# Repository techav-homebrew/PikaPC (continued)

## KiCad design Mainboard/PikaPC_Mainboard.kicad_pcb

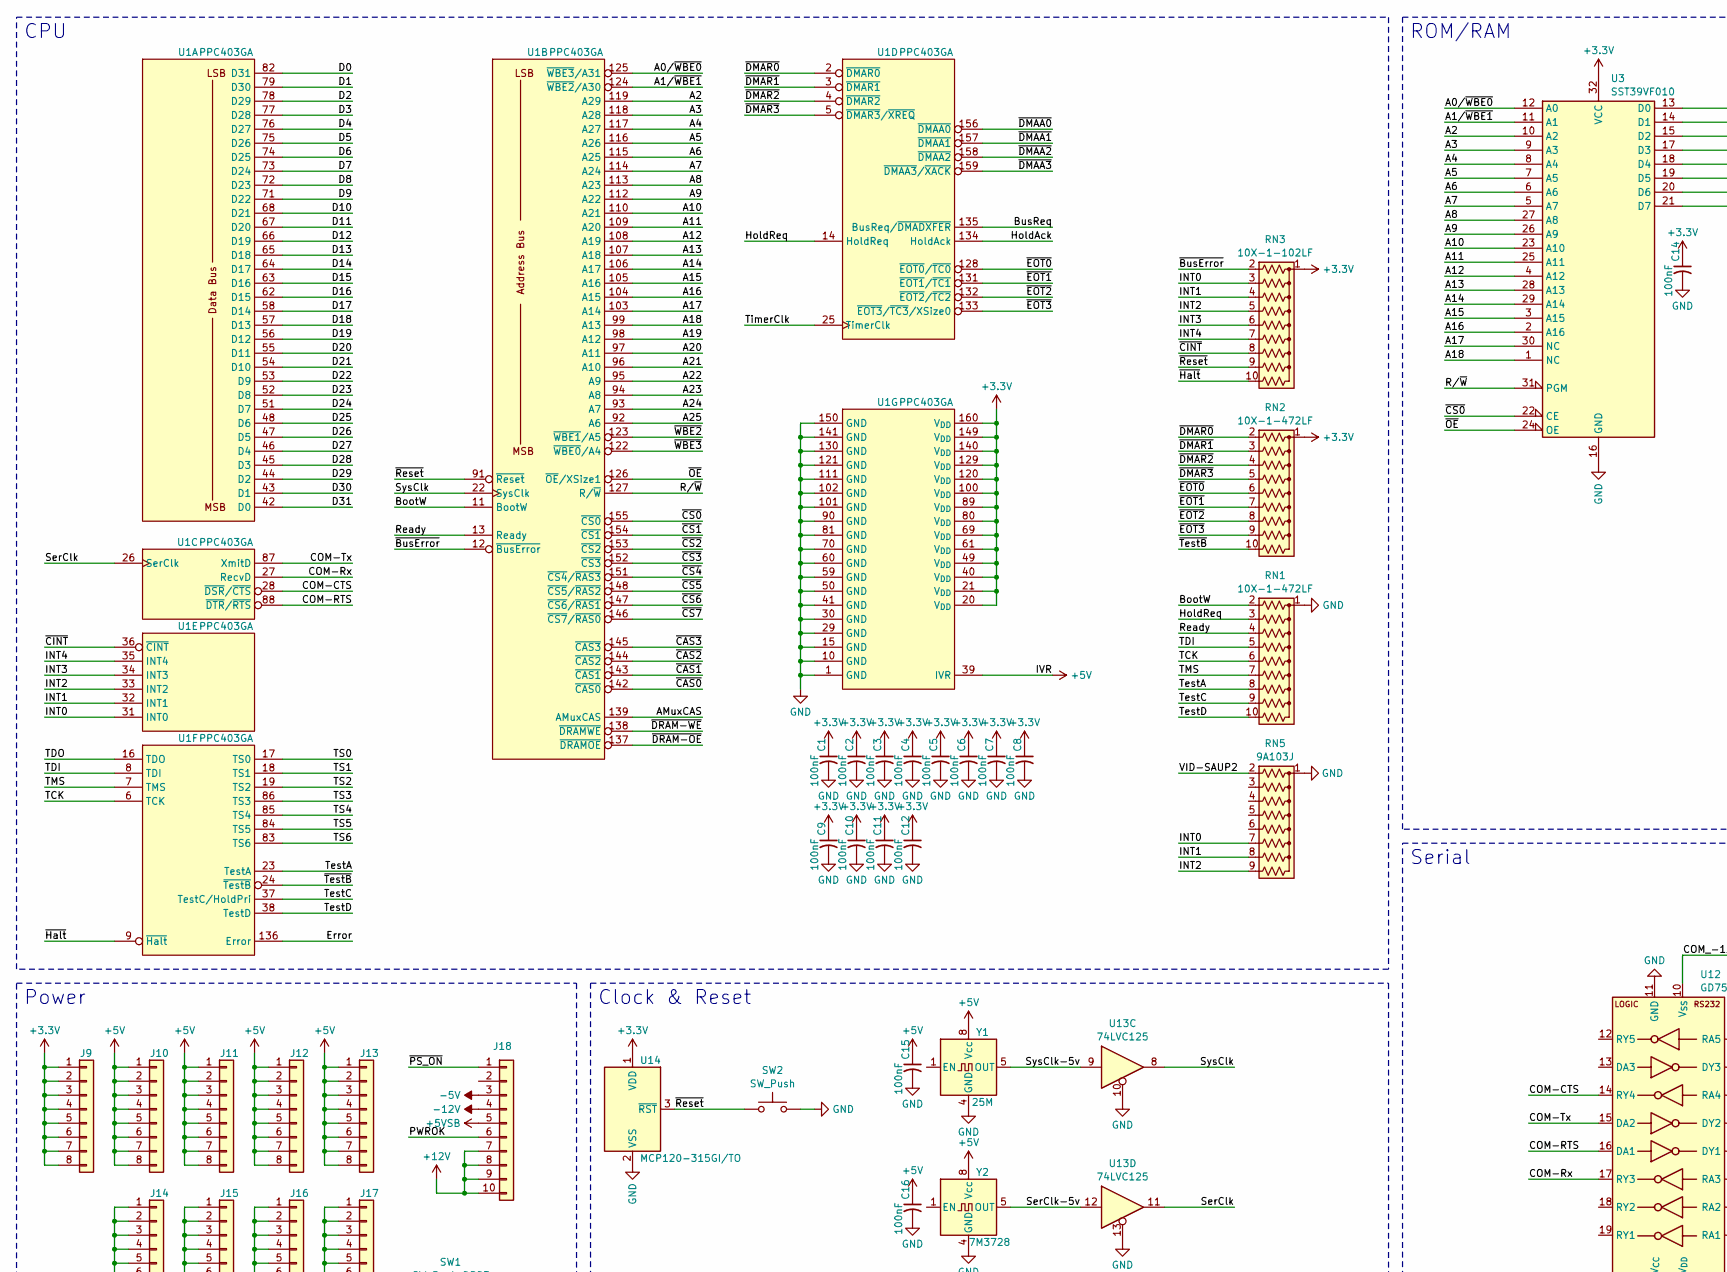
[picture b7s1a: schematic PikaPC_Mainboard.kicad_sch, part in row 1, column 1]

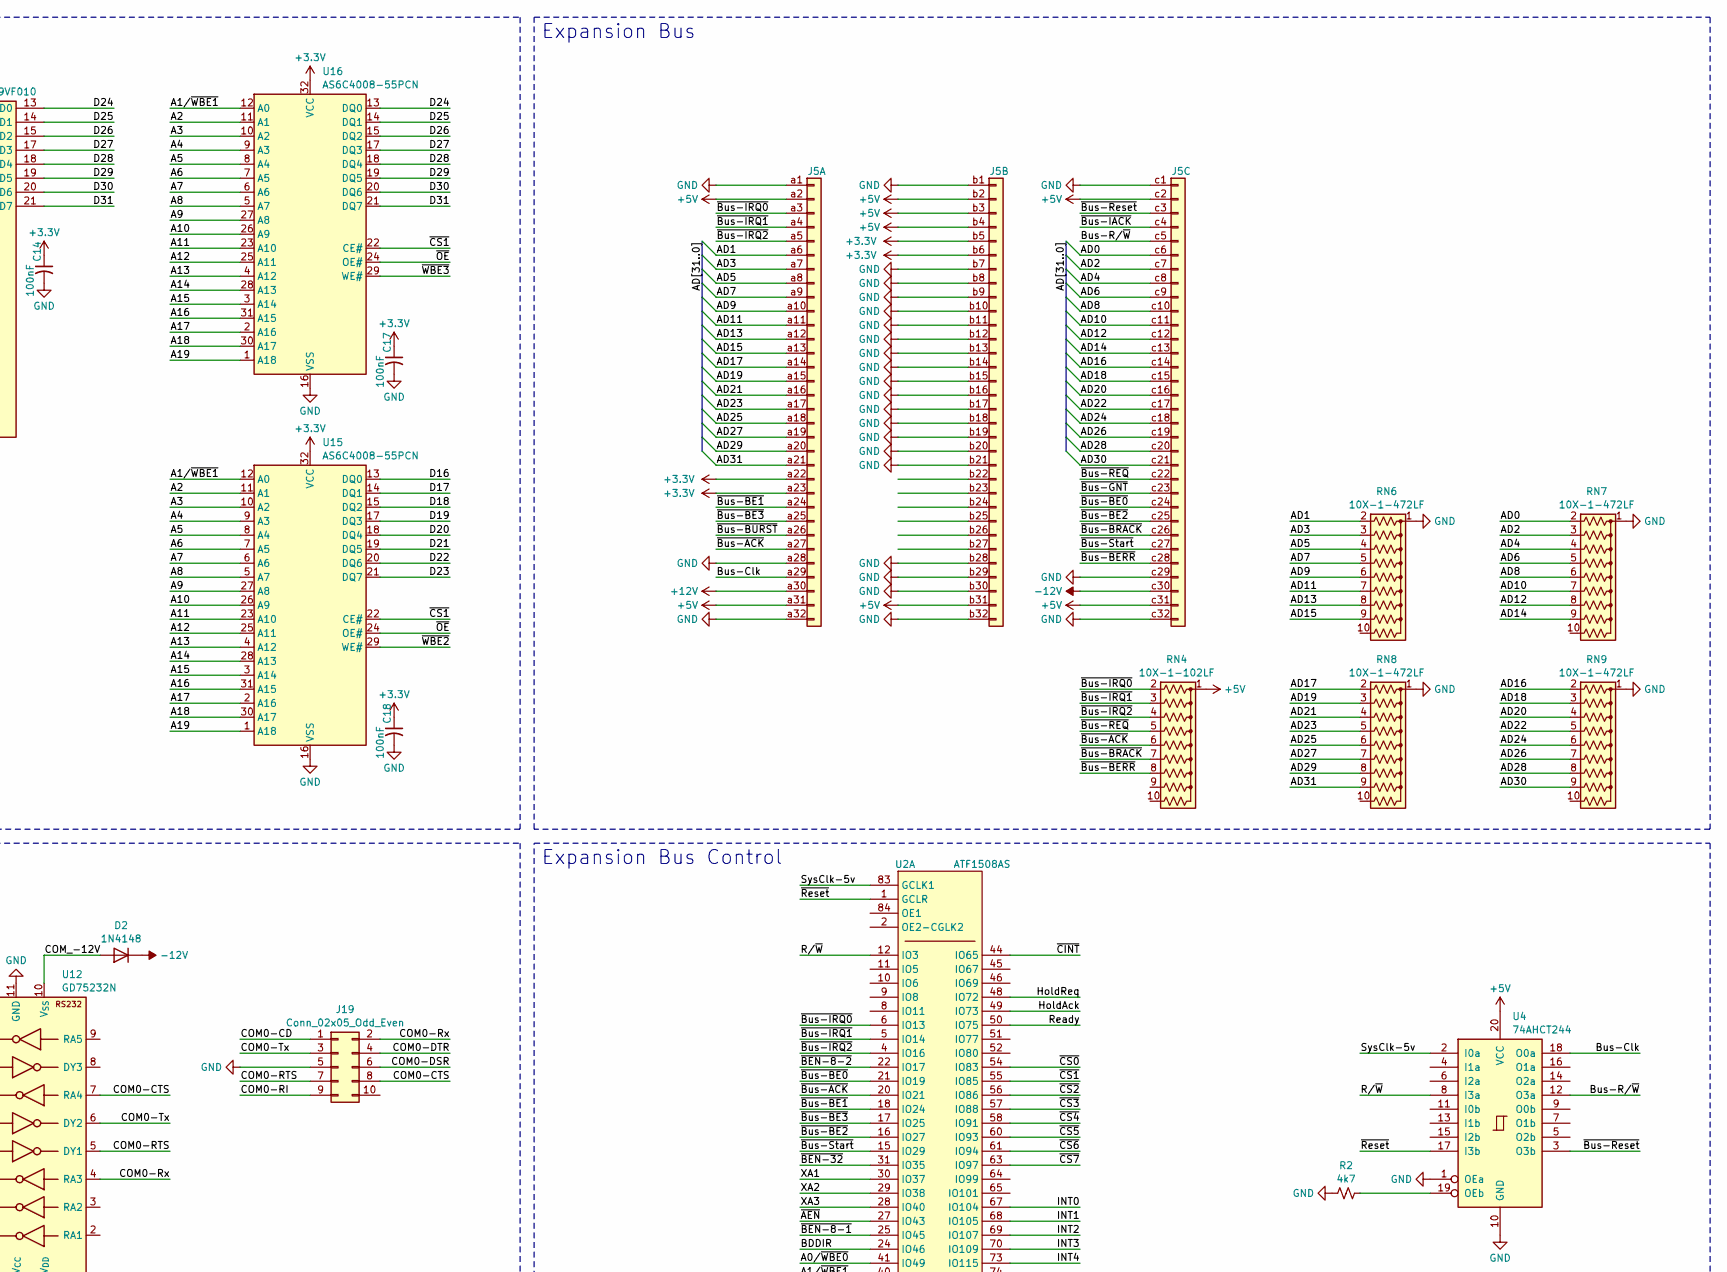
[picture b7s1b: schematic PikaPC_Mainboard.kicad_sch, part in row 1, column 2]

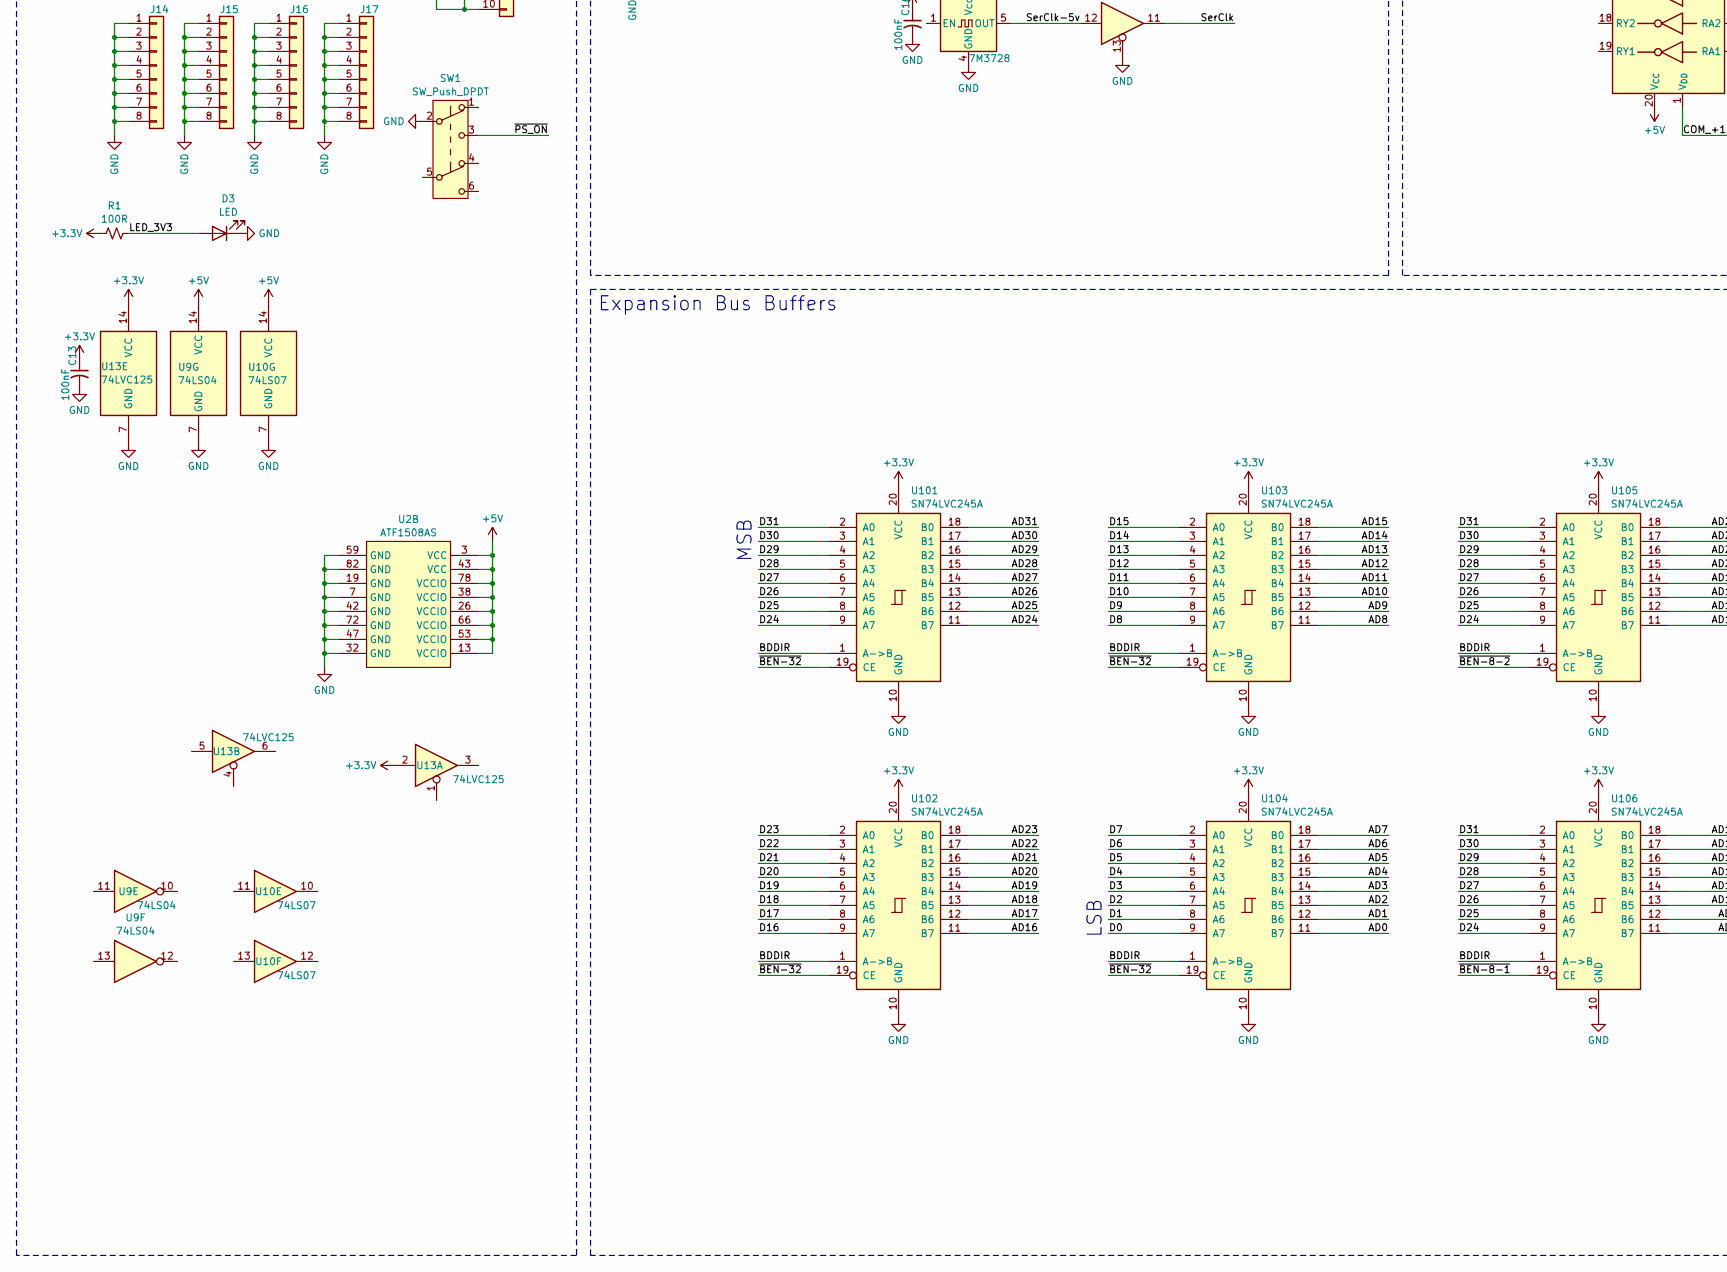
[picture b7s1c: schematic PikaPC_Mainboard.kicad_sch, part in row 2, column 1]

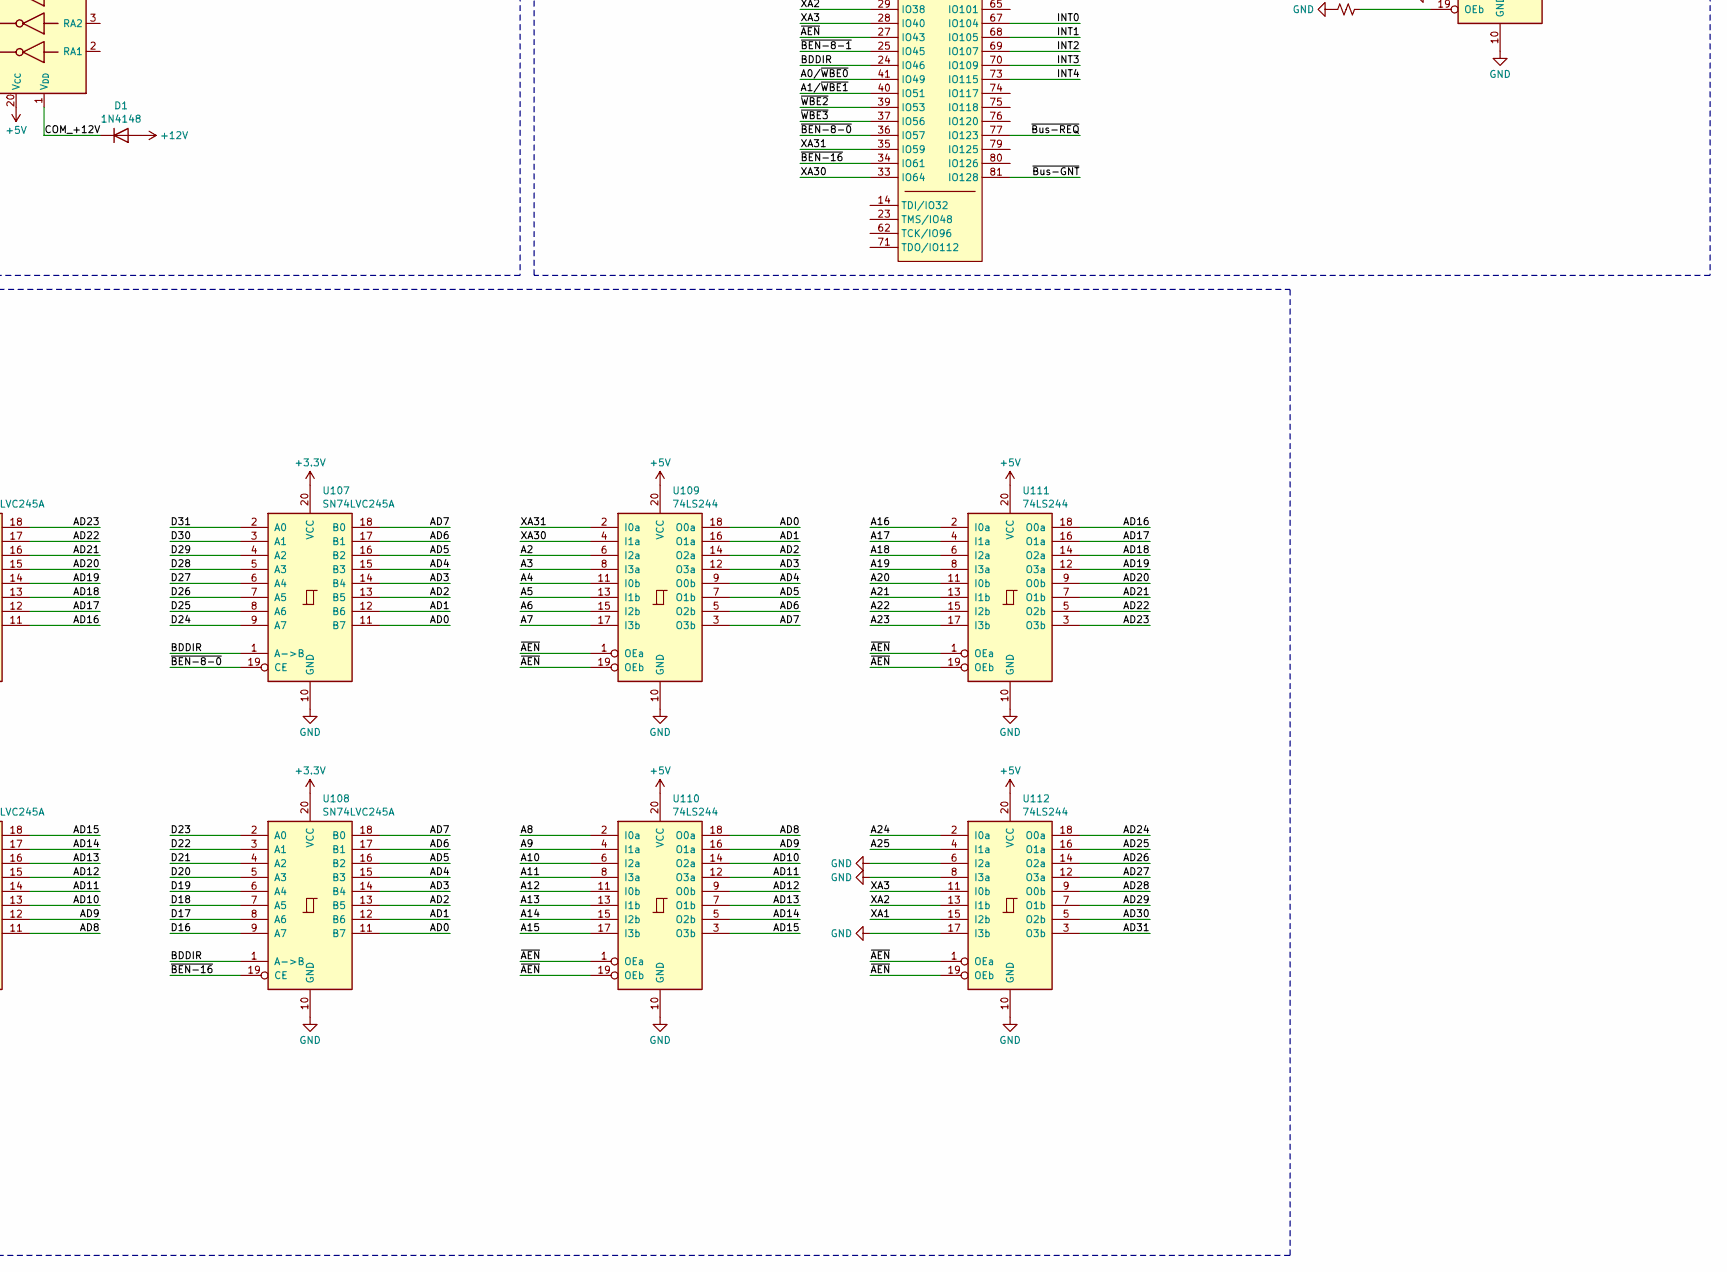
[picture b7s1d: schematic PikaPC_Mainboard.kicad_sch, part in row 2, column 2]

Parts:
C1, C2, C3, C4, C5, C6, C7, C8: 100nF; C_0805_2012Metric
C9, C10, C11, C12, C13: 100nF; C_Disc_D7.5mm_W5.0mm_P7.50mm
C14, C15, C16, C17, C18: 100nF; C_Disc_D3.0mm_W2.0mm_P2.50mm
D1, D2: 1N4148; D_DO-35_SOD27_P7.62mm_Horizontal
D3: LED; LED_D5.0mm
J5: DIN41612_03x32_C_Split; DIN41612_C_3x32_Female_Vertical_THT
J9, J10, J11, J12, J13, J14, J15, J16, J17: Conn_01x08; PinHeader_1x08_P2.54mm_Vertical
J18: Conn_01x10; PinHeader_1x10_P2.54mm_Vertical
J19: Conn_02x05_Odd_Even; PinHeader_2x05_P2.54mm_Vertical
R1: 100R; R_Axial_DIN0204_L3.6mm_D1.6mm_P2.54mm_Vertical
R2: 4k7; R_Axial_DIN0204_L3.6mm_D1.6mm_P7.62mm_Horizontal
RN1, RN2, RN6, RN7, RN8, RN9: 10X-1-472LF; R_Array_SIP10
RN3, RN4: 10X-1-102LF; R_Array_SIP10
RN5: 9A103J; R_Array_SIP9
SW1: SW_Push_DPDT; SW_CK_JS202011CQN_DPDT_Straight
SW2: SW_Push; SW_PUSH_6mm_H7.3mm
U1: PPC403GA; PQFP-160_28x28mm_P0.65mm
U2: ATF1508AS; PLCC-84_THT-Socket
U3: SST39VF010; PLCC-32_THT-Socket
U4: 74AHCT244; DIP-20_W7.62mm_Socket
U9: 74LS04; DIP-14_W7.62mm_Socket
U10: 74LS07; DIP-14_W7.62mm_Socket
U12: GD75232N; DIP-20_W7.62mm
U13: 74LVC125; DIP-14_W7.62mm_Socket
U14: MCP120-315GI/TO; TO-92_Inline_Wide
U15, U16: AS6C4008-55PCN; DIP-32_W15.24mm
U101, U102, U103, U104, U105, U106, U107, U108: SN74LVC245A; DIP-20_W7.62mm_Socket
U109, U110, U111, U112: 74LS244; DIP-20_W7.62mm_Socket
Y1: 25M; Oscillator_DIP-8
Y2: 7M3728; Oscillator_DIP-8

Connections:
+3.3V: C1.1, C2.1, C3.1, C4.1, C5.1, C6.1, C7.1, C8.1, C9.1, C10.1, C11.1, C12.1, C13.1, C14.1, C17.1, C18.1, J5.a22, J5.a23, J5.b5, J5.b6, J9.1, J9.2, J9.3, J9.4, J9.5, J9.6, J9.7, J9.8, R1.1, RN2.1 (common), RN3.1 (common), U1.20 (V_{DD}), U1.21 (V_{DD}), U1.40 (V_{DD}), U1.49 (V_{DD}), U1.61 (V_{DD}), U1.69 (V_{DD}), U1.80 (V_{DD}), U1.89 (V_{DD}), U1.100 (V_{DD}), U1.120 (V_{DD}), U1.129 (V_{DD}), U1.140 (V_{DD}), U1.149 (V_{DD}), U1.160 (V_{DD}), U3.32 (VCC), U13.2, U13.14 (VCC), U14.1 (VDD), U15.32 (VCC), U16.32 (VCC), U101.20 (VCC), U102.20 (VCC), U103.20 (VCC), U104.20 (VCC), U105.20 (VCC), U106.20 (VCC), U107.20 (VCC), U108.20 (VCC)
+5V: C15.1, C16.1, J5.a2, J5.a31, J5.b2, J5.b3, J5.b4, J5.b31, J5.c2, J5.c31, J10.1, J10.2, J10.3, J10.4, J10.5, J10.6, J10.7, J10.8, J11.1, J11.2, J11.3, J11.4, J11.5, J11.6, J11.7, J11.8, J12.1, J12.2, J12.3, J12.4, J12.5, J12.6, J12.7, J12.8, J13.1, J13.2, J13.3, J13.4, J13.5, J13.6, J13.7, J13.8, RN4.1 (common), U1.39 (IVR), U2.3 (VCC), U2.13 (VCCIO), U2.26 (VCCIO), U2.38 (VCCIO), U2.43 (VCC), U2.53 (VCCIO), U2.66 (VCCIO), U2.78 (VCCIO), U4.20 (VCC), U9.14 (VCC), U10.14 (VCC), U12.20 (V_{CC}), U109.20 (VCC), U110.20 (VCC), U111.20 (VCC), U112.20 (VCC), Y1.8 (Vcc), Y2.8 (Vcc)
+5VSB: J18.5
+12V: D1.2 (A), J5.a30, J18.7, J18.8, J18.9, J18.10
-5V: J18.3
-12V: D2.1 (K), J5.c30, J18.4
/A0/~WBE0: U1.125 (~WBE3/A31), U2.41 (IO49), U3.12 (A0)
/A1/~WBE1: U1.124 (~WBE2/A30), U2.40 (IO51), U3.11 (A1), U15.12 (A0), U16.12 (A0)
/A2: U1.119 (A29), U3.10 (A2), U15.11 (A1), U16.11 (A1), U109.6 (I2a)
/A3: U1.118 (A28), U3.9 (A3), U15.10 (A2), U16.10 (A2), U109.8 (I3a)
/A4: U1.117 (A27), U3.8 (A4), U15.9 (A3), U16.9 (A3), U109.11 (I0b)
/A5: U1.116 (A26), U3.7 (A5), U15.8 (A4), U16.8 (A4), U109.13 (I1b)
/A6: U1.115 (A25), U3.6 (A6), U15.7 (A5), U16.7 (A5), U109.15 (I2b)
/A7: U1.114 (A24), U3.5 (A7), U15.6 (A6), U16.6 (A6), U109.17 (I3b)
/A8: U1.113 (A23), U3.27 (A8), U15.5 (A7), U16.5 (A7), U110.2 (I0a)
/A9: U1.112 (A22), U3.26 (A9), U15.27 (A8), U16.27 (A8), U110.4 (I1a)
/A10: U1.110 (A21), U3.23 (A10), U15.26 (A9), U16.26 (A9), U110.6 (I2a)
/A11: U1.109 (A20), U3.25 (A11), U15.23 (A10), U16.23 (A10), U110.8 (I3a)
/A12: U1.108 (A19), U3.4 (A12), U15.25 (A11), U16.25 (A11), U110.11 (I0b)
/A13: U1.107 (A18), U3.28 (A13), U15.4 (A12), U16.4 (A12), U110.13 (I1b)
/A14: U1.106 (A17), U3.29 (A14), U15.28 (A13), U16.28 (A13), U110.15 (I2b)
/A15: U1.105 (A16), U3.3 (A15), U15.3 (A14), U16.3 (A14), U110.17 (I3b)
/A16: U1.104 (A15), U3.2 (A16), U15.31 (A15), U16.31 (A15), U111.2 (I0a)
/A17: U1.103 (A14), U3.30 (NC), U15.2 (A16), U16.2 (A16), U111.4 (I1a)
/A18: U1.99 (A13), U3.1 (NC), U15.30 (A17), U16.30 (A17), U111.6 (I2a)
/A19: U1.98 (A12), U15.1 (A18), U16.1 (A18), U111.8 (I3a)
/A20: U1.97 (A11), U111.11 (I0b)
/A21: U1.96 (A10), U111.13 (I1b)
/A22: U1.95 (A9), U111.15 (I2b)
/A23: U1.94 (A8), U111.17 (I3b)
/A24: U1.93 (A7), U112.2 (I0a)
/A25: U1.92 (A6), U112.4 (I1a)
/AD0: J5.c6, RN7.2 (R1), U104.11 (B7), U107.11 (B7), U108.11 (B7), U109.18 (O0a)
/AD1: J5.a6, RN6.2 (R1), U104.12 (B6), U107.12 (B6), U108.12 (B6), U109.16 (O1a)
/AD2: J5.c7, RN7.3 (R2), U104.13 (B5), U107.13 (B5), U108.13 (B5), U109.14 (O2a)
/AD3: J5.a7, RN6.3 (R2), U104.14 (B4), U107.14 (B4), U108.14 (B4), U109.12 (O3a)
/AD4: J5.c8, RN7.4 (R3), U104.15 (B3), U107.15 (B3), U108.15 (B3), U109.9 (O0b)
/AD5: J5.a8, RN6.4 (R3), U104.16 (B2), U107.16 (B2), U108.16 (B2), U109.7 (O1b)
/AD6: J5.c9, RN7.5 (R4), U104.17 (B1), U107.17 (B1), U108.17 (B1), U109.5 (O2b)
/AD7: J5.a9, RN6.5 (R4), U104.18 (B0), U107.18 (B0), U108.18 (B0), U109.3 (O3b)
/AD8: J5.c10, RN7.6 (R5), U103.11 (B7), U106.11 (B7), U110.18 (O0a)
/AD9: J5.a10, RN6.6 (R5), U103.12 (B6), U106.12 (B6), U110.16 (O1a)
/AD10: J5.c11, RN7.7 (R6), U103.13 (B5), U106.13 (B5), U110.14 (O2a)
/AD11: J5.a11, RN6.7 (R6), U103.14 (B4), U106.14 (B4), U110.12 (O3a)
/AD12: J5.c12, RN7.8 (R7), U103.15 (B3), U106.15 (B3), U110.9 (O0b)
/AD13: J5.a12, RN6.8 (R7), U103.16 (B2), U106.16 (B2), U110.7 (O1b)
/AD14: J5.c13, RN7.9 (R8), U103.17 (B1), U106.17 (B1), U110.5 (O2b)
/AD15: J5.a13, RN6.9 (R8), U103.18 (B0), U106.18 (B0), U110.3 (O3b)
/AD16: J5.c14, RN9.2 (R1), U102.11 (B7), U105.11 (B7), U111.18 (O0a)
/AD17: J5.a14, RN8.2 (R1), U102.12 (B6), U105.12 (B6), U111.16 (O1a)
/AD18: J5.c15, RN9.3 (R2), U102.13 (B5), U105.13 (B5), U111.14 (O2a)
/AD19: J5.a15, RN8.3 (R2), U102.14 (B4), U105.14 (B4), U111.12 (O3a)
/AD20: J5.c16, RN9.4 (R3), U102.15 (B3), U105.15 (B3), U111.9 (O0b)
/AD21: J5.a16, RN8.4 (R3), U102.16 (B2), U105.16 (B2), U111.7 (O1b)
/AD22: J5.c17, RN9.5 (R4), U102.17 (B1), U105.17 (B1), U111.5 (O2b)
/AD23: J5.a17, RN8.5 (R4), U102.18 (B0), U105.18 (B0), U111.3 (O3b)
/AD24: J5.c18, RN9.6 (R5), U101.11 (B7), U112.18 (O0a)
/AD25: J5.a18, RN8.6 (R5), U101.12 (B6), U112.16 (O1a)
/AD26: J5.c19, RN9.7 (R6), U101.13 (B5), U112.14 (O2a)
/AD27: J5.a19, RN8.7 (R6), U101.14 (B4), U112.12 (O3a)
/AD28: J5.c20, RN9.8 (R7), U101.15 (B3), U112.9 (O0b)
/AD29: J5.a20, RN8.8 (R7), U101.16 (B2), U112.7 (O1b)
/AD30: J5.c21, RN9.9 (R8), U101.17 (B1), U112.5 (O2b)
/AD31: J5.a21, RN8.9 (R8), U101.18 (B0), U112.3 (O3b)
/AMuxCAS: U1.139 (AMuxCAS)
/BDDIR: U2.24 (IO46), U101.1 (A->B), U102.1 (A->B), U103.1 (A->B), U104.1 (A->B), U105.1 (A->B), U106.1 (A->B), U107.1 (A->B), U108.1 (A->B)
/BootW: RN1.2 (R1), U1.11 (BootW)
/Bus-Clk: J5.a29, U4.18 (O0a)
/Bus-R/~W: J5.c5, U4.12 (O3a)
/BusReq: U1.135 (BusReq/~DMADXFER)
/COM0-CD: J19.1
/COM0-CTS: J19.8, U12.7 (RA4)
/COM0-DSR: J19.6
/COM0-DTR: J19.4
/COM0-RI: J19.9
/COM0-RTS: J19.7, U12.5 (DY1)
/COM0-Rx: J19.2, U12.4 (RA3)
/COM0-Tx: J19.3, U12.6 (DY2)
/COM-CTS: U1.28 (~DSR/~CTS), U12.14 (RY4)
/COM-RTS: U1.88 (~DTR/~RTS), U12.16 (DA1)
/COM-Rx: U1.27 (RecvD), U12.17 (RY3)
/COM-Tx: U1.87 (XmitD), U12.15 (DA2)
/COM_+12V: D1.1 (K), U12.1 (V_{DD})
/COM_-12V: D2.2 (A), U12.10 (V_{SS})
/D0: U1.82 (D31), U104.9 (A7)
/D1: U1.79 (D30), U104.8 (A6)
/D2: U1.78 (D29), U104.7 (A5)
/D3: U1.77 (D28), U104.6 (A4)
/D4: U1.76 (D27), U104.5 (A3)
/D5: U1.75 (D26), U104.4 (A2)
/D6: U1.74 (D25), U104.3 (A1)
/D7: U1.73 (D24), U104.2 (A0)
/D8: U1.72 (D23), U103.9 (A7)
/D9: U1.71 (D22), U103.8 (A6)
/D10: U1.68 (D21), U103.7 (A5)
/D11: U1.67 (D20), U103.6 (A4)
/D12: U1.66 (D19), U103.5 (A3)
/D13: U1.65 (D18), U103.4 (A2)
/D14: U1.64 (D17), U103.3 (A1)
/D15: U1.63 (D16), U103.2 (A0)
/D16: U1.62 (D15), U15.13 (DQ0), U102.9 (A7), U108.9 (A7)
/D17: U1.58 (D14), U15.14 (DQ1), U102.8 (A6), U108.8 (A6)
/D18: U1.57 (D13), U15.15 (DQ2), U102.7 (A5), U108.7 (A5)
/D19: U1.56 (D12), U15.17 (DQ3), U102.6 (A4), U108.6 (A4)
/D20: U1.55 (D11), U15.18 (DQ4), U102.5 (A3), U108.5 (A3)
/D21: U1.54 (D10), U15.19 (DQ5), U102.4 (A2), U108.4 (A2)
/D22: U1.53 (D9), U15.20 (DQ6), U102.3 (A1), U108.3 (A1)
/D23: U1.52 (D8), U15.21 (DQ7), U102.2 (A0), U108.2 (A0)
/D24: U1.51 (D7), U3.13 (D0), U16.13 (DQ0), U101.9 (A7), U105.9 (A7), U106.9 (A7), U107.9 (A7)
/D25: U1.48 (D6), U3.14 (D1), U16.14 (DQ1), U101.8 (A6), U105.8 (A6), U106.8 (A6), U107.8 (A6)
/D26: U1.47 (D5), U3.15 (D2), U16.15 (DQ2), U101.7 (A5), U105.7 (A5), U106.7 (A5), U107.7 (A5)
/D27: U1.46 (D4), U3.17 (D3), U16.17 (DQ3), U101.6 (A4), U105.6 (A4), U106.6 (A4), U107.6 (A4)
/D28: U1.45 (D3), U3.18 (D4), U16.18 (DQ4), U101.5 (A3), U105.5 (A3), U106.5 (A3), U107.5 (A3)
/D29: U1.44 (D2), U3.19 (D5), U16.19 (DQ5), U101.4 (A2), U105.4 (A2), U106.4 (A2), U107.4 (A2)
/D30: U1.43 (D1), U3.20 (D6), U16.20 (DQ6), U101.3 (A1), U105.3 (A1), U106.3 (A1), U107.3 (A1)
/D31: U1.42 (D0), U3.21 (D7), U16.21 (DQ7), U101.2 (A0), U105.2 (A0), U106.2 (A0), U107.2 (A0)
/Error: U1.136 (Error)
/HoldAck: U1.134 (HoldAck), U2.49 (IO73)
/HoldReq: RN1.3 (R2), U1.14 (HoldReq), U2.48 (IO72)
/INT0: RN3.3 (R2), RN5.7 (R6), U1.31 (INT0), U2.67 (IO104)
/INT1: RN3.4 (R3), RN5.8 (R7), U1.32 (INT1), U2.68 (IO105)
/INT2: RN3.5 (R4), RN5.9 (R8), U1.33 (INT2), U2.69 (IO107)
/INT3: RN3.6 (R5), U1.34 (INT3), U2.70 (IO109)
/INT4: RN3.7 (R6), U1.35 (INT4), U2.73 (IO115)
/LED_3V3: D3.2 (A), R1.2
/PWROK: J18.6
/Ready: RN1.4 (R3), U1.13 (Ready), U2.50 (IO75)
/R/~W: U1.127 (R/~W), U2.12 (IO3), U3.31 (PGM), U4.8 (I3a)
/SerClk: U1.26 (SerClk), U13.11
/SerClk-5v: U13.12, Y2.5 (OUT)
/SysClk: U1.22 (SysClk), U13.8
/SysClk-5v: U2.83 (GCLK1), U4.2 (I0a), U13.9, Y1.5 (OUT)
/TCK: RN1.6 (R5), U1.6 (TCK)
/TDI: RN1.5 (R4), U1.8 (TDI)
/TDO: U1.16 (TDO)
/TMS: RN1.7 (R6), U1.7 (TMS)
/TS0: U1.17 (TS0)
/TS1: U1.18 (TS1)
/TS2: U1.19 (TS2)
/TS3: U1.86 (TS3)
/TS4: U1.85 (TS4)
/TS5: U1.84 (TS5)
/TS6: U1.83 (TS6)
/TestA: RN1.8 (R7), U1.23 (TestA)
/TestC: RN1.9 (R8), U1.37 (TestC/HoldPri)
/TestD: RN1.10 (R9), U1.38 (TestD)
/TimerClk: U1.25 (TimerClk)
/VID-SAUP2: RN5.2 (R1)
/XA1: U2.30 (IO37), U112.15 (I2b)
/XA2: U2.29 (IO38), U112.13 (I1b)
/XA3: U2.28 (IO40), U112.11 (I0b)
/XA30: U2.33 (IO64), U109.4 (I1a)
/XA31: U2.35 (IO59), U109.2 (I0a)
/~AEN: U2.27 (IO43), U109.1 (OEa), U109.19 (OEb), U110.1 (OEa), U110.19 (OEb), U111.1 (OEa), U111.19 (OEb), U112.1 (OEa), U112.19 (OEb)
/~BEN-8-0: U2.36 (IO57), U107.19 (CE)
/~BEN-8-1: U2.25 (IO45), U106.19 (CE)
/~BEN-8-2: U2.22 (IO17), U105.19 (CE)
/~BEN-16: U2.34 (IO61), U108.19 (CE)
/~BEN-32: U2.31 (IO35), U101.19 (CE), U102.19 (CE), U103.19 (CE), U104.19 (CE)
/~Bus-ACK: J5.a27, RN4.6 (R5), U2.20 (IO21)
/~Bus-BE0: J5.c24, U2.21 (IO19)
/~Bus-BE1: J5.a24, U2.18 (IO24)
/~Bus-BE2: J5.c25, U2.16 (IO27)
/~Bus-BE3: J5.a25, U2.17 (IO25)
/~Bus-BERR: J5.c28, RN4.8 (R7)
/~Bus-BRACK: J5.c26, RN4.7 (R6)
/~Bus-BURST: J5.a26
/~Bus-GNT: J5.c23, U2.81 (IO128)
/~Bus-IACK: J5.c4
/~Bus-IRQ0: J5.a3, RN4.2 (R1), U2.6 (IO13)
/~Bus-IRQ1: J5.a4, RN4.3 (R2), U2.5 (IO14)
/~Bus-IRQ2: J5.a5, RN4.4 (R3), U2.4 (IO16)
/~Bus-REQ: J5.c22, RN4.5 (R4), U2.77 (IO123)
/~Bus-Reset: J5.c3, U4.3 (O3b)
/~Bus-Start: J5.c27, U2.15 (IO29)
/~BusError: RN3.2 (R1), U1.12 (~BusError)
/~CAS0: U1.142 (~CAS0)
/~CAS1: U1.143 (~CAS1)
/~CAS2: U1.144 (~CAS2)
/~CAS3: U1.145 (~CAS3)
/~CINT: RN3.8 (R7), U1.36 (~CINT), U2.44 (IO65)
/~CS0: U1.155 (~CS0), U2.54 (IO83), U3.22 (CE)
/~CS1: U1.154 (~CS1), U2.55 (IO85), U15.22 (CE#), U16.22 (CE#)
/~CS2: U1.153 (~CS2), U2.56 (IO86)
/~CS3: U1.152 (~CS3), U2.57 (IO88)
/~CS4: U1.151 (~CS4/~RAS3), U2.58 (IO91)
/~CS5: U1.148 (~CS5/~RAS2), U2.60 (IO93)
/~CS6: U1.147 (~CS6/~RAS1), U2.61 (IO94)
/~CS7: U1.146 (~CS7/~RAS0), U2.63 (IO97)
/~DMAA0: U1.156 (~DMAA0)
/~DMAA1: U1.157 (~DMAA1)
/~DMAA2: U1.158 (~DMAA2)
/~DMAA3: U1.159 (~DMAA3/~XACK)
/~DMAR0: RN2.2 (R1), U1.2 (~DMAR0)
/~DMAR1: RN2.3 (R2), U1.3 (~DMAR1)
/~DMAR2: RN2.4 (R3), U1.4 (~DMAR2)
/~DMAR3: RN2.5 (R4), U1.5 (~DMAR3/~XREQ)
/~DRAM-OE: U1.137 (~DRAMOE)
/~DRAM-WE: U1.138 (~DRAMWE)
/~EOT0: RN2.6 (R5), U1.128 (~EOT0/~TC0)
/~EOT1: RN2.7 (R6), U1.131 (~EOT1/~TC1)
/~EOT2: RN2.8 (R7), U1.132 (~EOT2/~TC2)
/~EOT3: RN2.9 (R8), U1.133 (~EOT3/~TC3/XSize0)
/~Halt: RN3.10 (R9), U1.9 (~Halt)
/~OE: U1.126 (~OE/XSize1), U3.24 (OE), U15.24 (OE#), U16.24 (OE#)
/~PS_ON: J18.1, SW1.3 (C)
/~Reset: RN3.9 (R8), SW2.2, U1.91 (~Reset), U2.1 (GCLR), U4.17 (I3b), U14.3 (~RST)
/~TestB: RN2.10 (R9), U1.24 (~TestB)
/~WBE2: U1.123 (~WBE1/A5), U2.39 (IO53), U15.29 (WE#)
/~WBE3: U1.122 (~WBE0/A4), U2.37 (IO56), U16.29 (WE#)
GND: C1.2, C2.2, C3.2, C4.2, C5.2, C6.2, C7.2, C8.2, C9.2, C10.2, C11.2, C12.2, C13.2, C14.2, C15.2, C16.2, C17.2, C18.2, D3.1 (K), J5.a1, J5.a28, J5.a32, J5.b1, J5.b7, J5.b8, J5.b9, J5.b10, J5.b11, J5.b12, J5.b13, J5.b14, J5.b15, J5.b16, J5.b17, J5.b18, J5.b19, J5.b20, J5.b21, J5.b28, J5.b29, J5.b30, J5.b32, J5.c1, J5.c29, J5.c32, J14.1, J14.2, J14.3, J14.4, J14.5, J14.6, J14.7, J14.8, J15.1, J15.2, J15.3, J15.4, J15.5, J15.6, J15.7, J15.8, J16.1, J16.2, J16.3, J16.4, J16.5, J16.6, J16.7, J16.8, J17.1, J17.2, J17.3, J17.4, J17.5, J17.6, J17.7, J17.8, J19.5, R2.1, RN1.1 (common), RN5.1 (common), RN6.1 (common), RN7.1 (common), RN8.1 (common), RN9.1 (common), SW1.2 (B), SW2.1, U1.1 (GND), U1.10 (GND), U1.15 (GND), U1.29 (GND), U1.30 (GND), U1.41 (GND), U1.50 (GND), U1.59 (GND), U1.60 (GND), U1.70 (GND), U1.81 (GND), U1.90 (GND), U1.101 (GND), U1.102 (GND), U1.111 (GND), U1.121 (GND), U1.130 (GND), U1.141 (GND), U1.150 (GND), U2.7 (GND), U2.19 (GND), U2.32 (GND), U2.42 (GND), U2.47 (GND), U2.59 (GND), U2.72 (GND), U2.82 (GND), U3.16 (GND), U4.1 (OEa), U4.10 (GND), U9.7 (GND), U10.7 (GND), U12.11 (GND), U13.7 (GND), U13.10, U13.13, U14.2 (VSS), U15.16 (VSS), U16.16 (VSS), U101.10 (GND), U102.10 (GND), U103.10 (GND), U104.10 (GND), U105.10 (GND), U106.10 (GND), U107.10 (GND), U108.10 (GND), U109.10 (GND), U110.10 (GND), U111.10 (GND), U112.6 (I2a), U112.8 (I3a), U112.10 (GND), U112.17 (I3b), Y1.4 (GND), Y2.4 (GND)
unnamed: R2.2, U4.19 (OEb)

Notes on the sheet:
Power
Expansion Bus Control
LSB
CPU
ROM/RAM
Serial
Expansion Bus
MSB
Clock & Reset
Expansion Bus Buffers

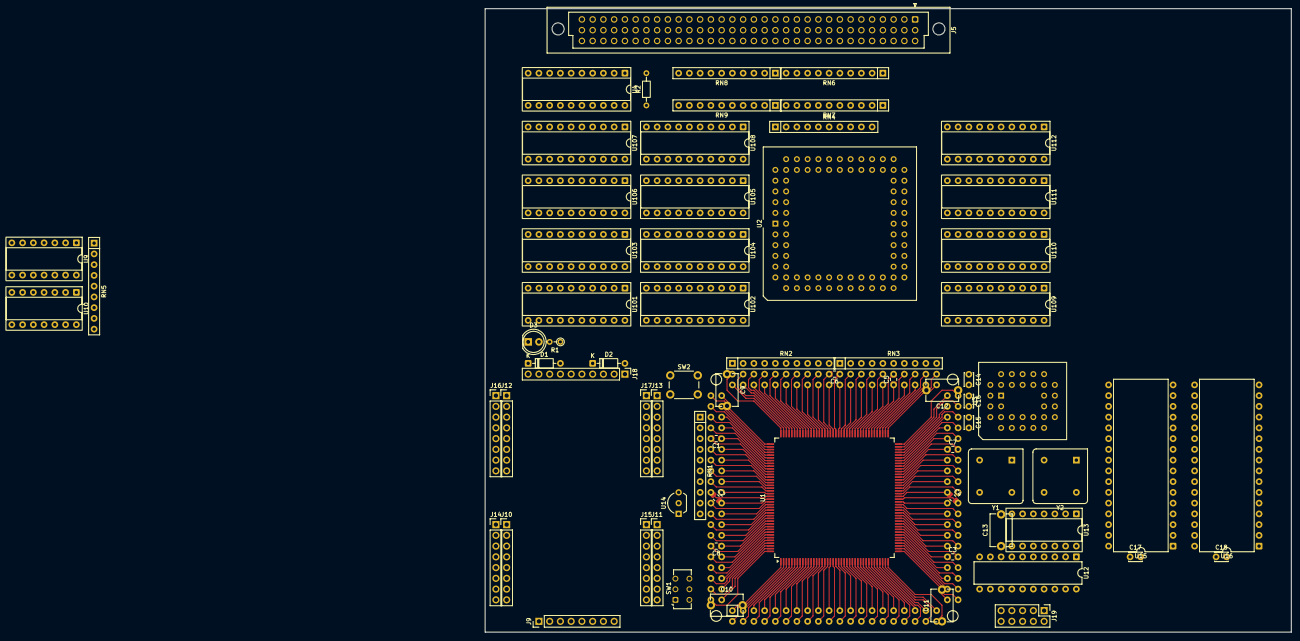
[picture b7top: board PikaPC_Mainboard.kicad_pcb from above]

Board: 2 copper layers, 190.5 x 147.3 mm, 71 parts (0 on the bottom side), 180 nets.

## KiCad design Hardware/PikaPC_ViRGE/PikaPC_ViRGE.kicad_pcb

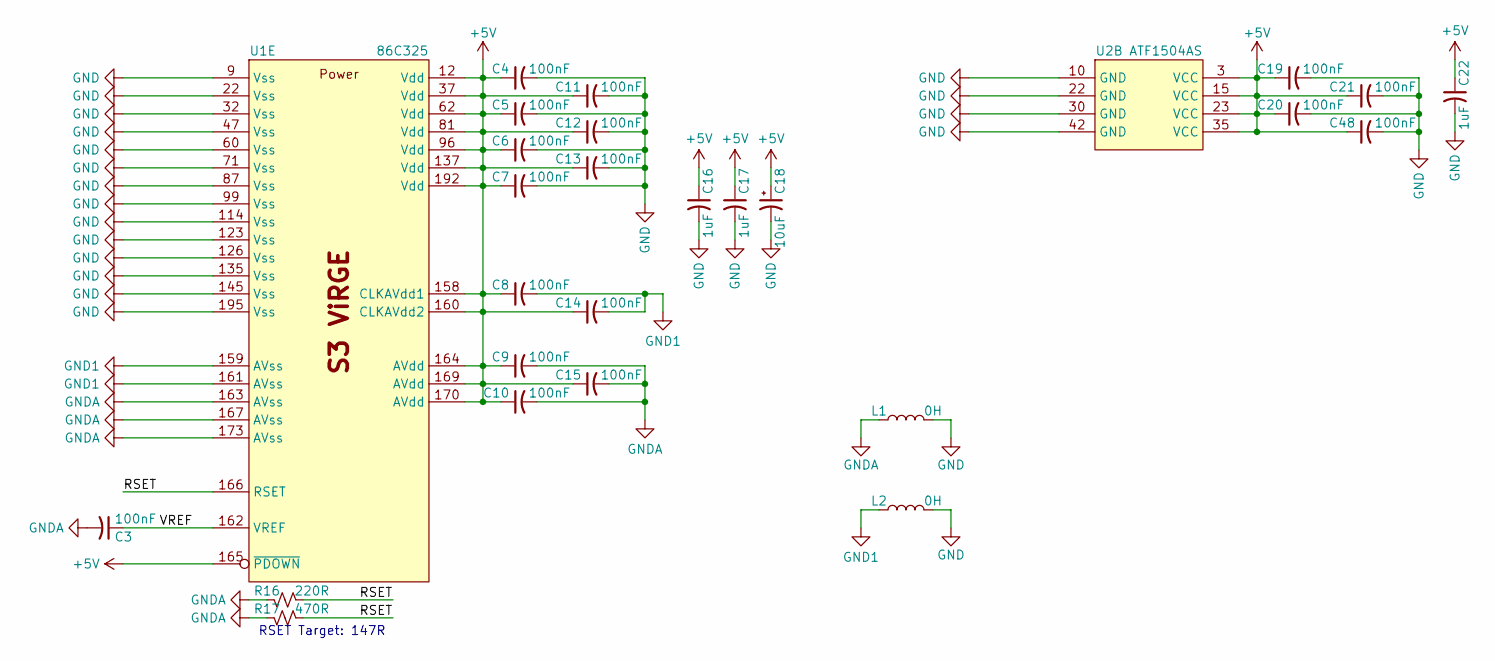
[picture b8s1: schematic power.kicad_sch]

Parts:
C3, C4, C5, C6, C7, C8, C9, C10, C11, C12, C13, C14, C15, C19, C20, C21, C48: 100nF; C_0805_2012Metric
C16, C17, C22: 1uF; C_0805_2012Metric
C18: 10uF; CP_Elec_4x5.7; Mouser 80-EDK106M016A9BAA
L1, L2: 0H; L_1210_3225Metric
R16: 220R; R_Axial_DIN0204_L3.6mm_D1.6mm_P2.54mm_Vertical
R17: 470R; R_Axial_DIN0204_L3.6mm_D1.6mm_P2.54mm_Vertical
U1: 86C325; PQFP-208_28x28mm_P0.5mm
U2: ATF1504AS; PLCC-44_THT-Socket

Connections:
+5V: C4.1, C5.1, C6.1, C7.1, C8.1, C9.1, C10.1, C11.1, C12.1, C13.1, C14.1, C15.1, C16.1, C17.1, C18.1, C19.1, C20.1, C21.1, C22.1, C48.1, U1.12 (Vdd), U1.37 (Vdd), U1.62 (Vdd), U1.81 (Vdd), U1.96 (Vdd), U1.137 (Vdd), U1.158 (CLKAVdd1), U1.160 (CLKAVdd2), U1.164 (AVdd), U1.165 (~PDOWN), U1.169 (AVdd), U1.170 (AVdd), U1.192 (Vdd), U2.3 (VCC), U2.15 (VCC), U2.23 (VCC), U2.35 (VCC); also elsewhere on the board
/Power/RSET: R16.1, R17.1, U1.166 (RSET); also elsewhere on the board
/Power/VREF: C3.1, U1.162 (VREF)
GND: C4.2, C5.2, C6.2, C7.2, C11.2, C12.2, C13.2, C16.2, C17.2, C18.2, C19.2, C20.2, C21.2, C22.2, C48.2, L1.2, L2.2, U1.9 (Vss), U1.22 (Vss), U1.32 (Vss), U1.47 (Vss), U1.60 (Vss), U1.71 (Vss), U1.87 (Vss), U1.99 (Vss), U1.114 (Vss), U1.123 (Vss), U1.126 (Vss), U1.135 (Vss), U1.145 (Vss), U1.195 (Vss), U2.10 (GND), U2.22 (GND), U2.30 (GND), U2.42 (GND); also elsewhere on the board
GND1: C8.2, C14.2, L2.1, U1.159 (AVss), U1.161 (AVss); also elsewhere on the board
GNDA: C3.2, C9.2, C10.2, C15.2, L1.1, R16.2, R17.2, U1.163 (AVss), U1.167 (AVss), U1.173 (AVss); also elsewhere on the board

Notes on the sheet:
RSET Target: 147R

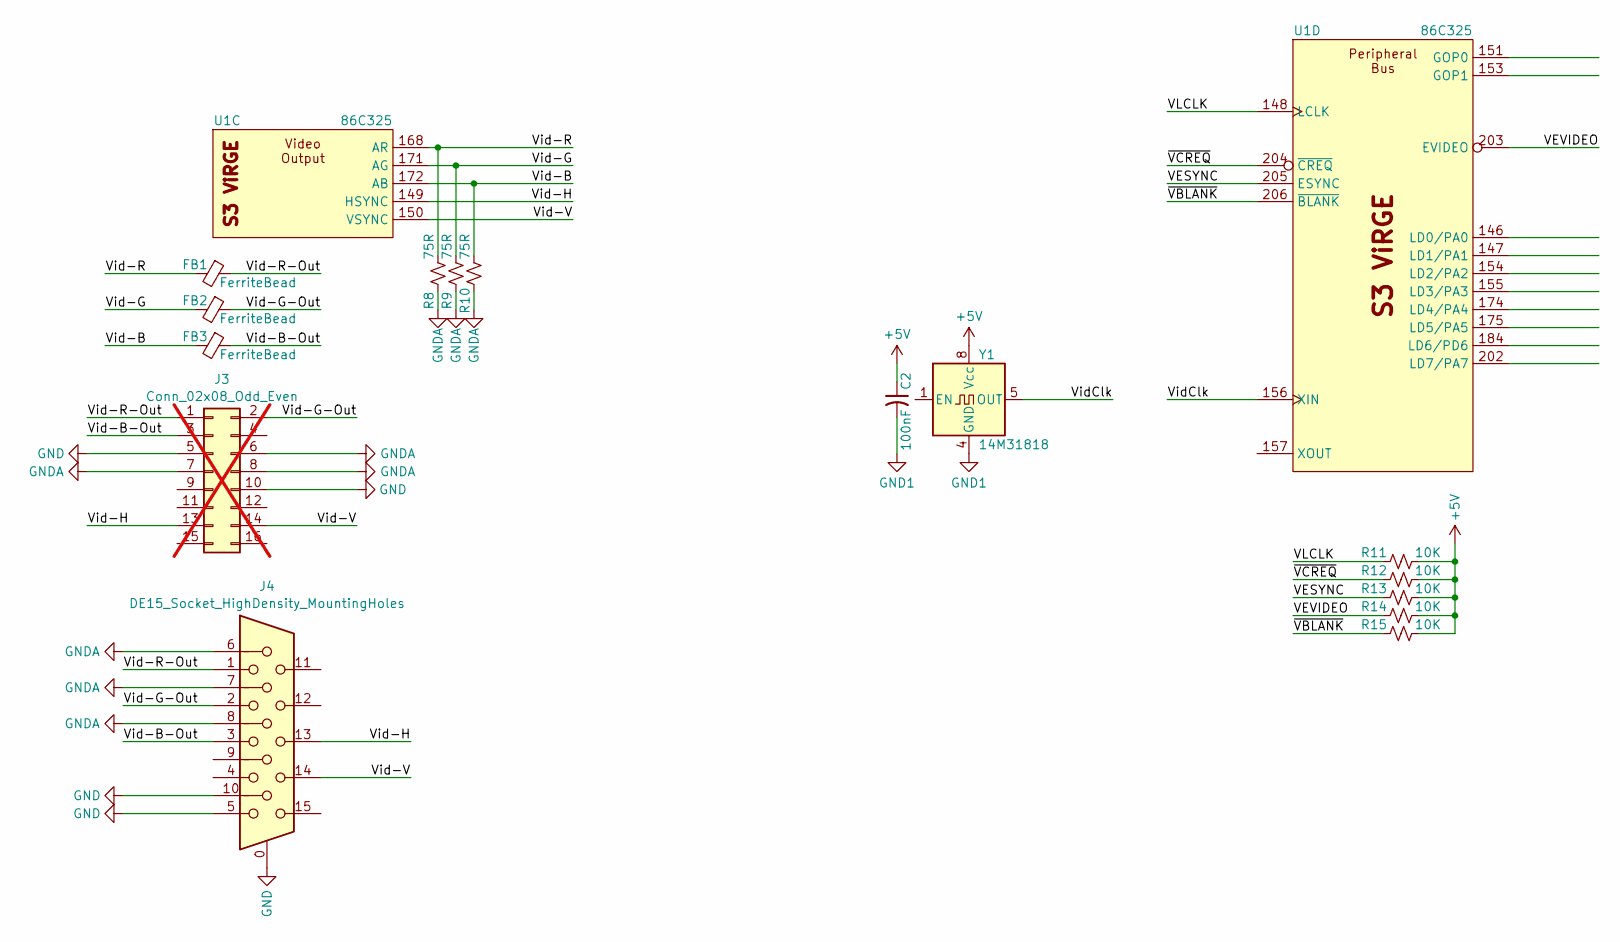
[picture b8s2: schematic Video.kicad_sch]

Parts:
C2: 100nF; C_0805_2012Metric; Mouser 187-CL21B104KACNNNC
FB1, FB2, FB3: FerriteBead; L_Axial_L5.3mm_D2.2mm_P2.54mm_Vertical_Vishay_IM-1
J3: Conn_02x08_Odd_Even; PinHeader_2x08_P2.54mm_Vertical; not fitted
J4: DE15_Socket_HighDensity_MountingHoles; DE15 (EDAC 634-015); Mouser 587-634-015-263-032
R8, R9, R10: 75R; R_0805_2012Metric; Mouser 603-RC0805FR-1375RL
R11, R12, R13, R14, R15: 10K; R_0805_2012Metric; Mouser 303-0805S8J0103T5E
U1: 86C325; PQFP-208_28x28mm_P0.5mm
Y1: 14M31818; Oscillator_DIP-8

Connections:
+5V: C2.1, R11.2, R12.2, R13.2, R14.2, R15.2, Y1.8 (Vcc); also elsewhere on the board
/Video/VESYNC: R13.1, U1.205 (ESYNC)
/Video/VEVIDEO: R14.1, U1.203 (EVIDEO)
/Video/VLCLK: R11.1, U1.148 (LCLK)
/Video/Vid-B: FB3.2, R10.2, U1.172 (AB)
/Video/Vid-B-Out: FB3.1, J3.3, J4.3
/Video/Vid-G: FB2.2, R9.2, U1.171 (AG)
/Video/Vid-G-Out: FB2.1, J3.2, J4.2
/Video/Vid-H: J3.13, J4.13, U1.149 (HSYNC)
/Video/Vid-R: FB1.2, R8.2, U1.168 (AR)
/Video/Vid-R-Out: FB1.1, J3.1, J4.1
/Video/Vid-V: J3.14, J4.14, U1.150 (VSYNC)
/Video/VidClk: U1.156 (XIN), Y1.5 (OUT)
/Video/~VBLANK: R15.1, U1.206 (~BLANK)
/Video/~VCREQ: R12.1, U1.204 (~CREQ)
GND: J3.5, J3.10, J4.0, J4.5, J4.10; also elsewhere on the board
GND1: C2.2, Y1.4 (GND); also elsewhere on the board
GNDA: J3.6, J3.7, J3.8, J4.6, J4.7, J4.8, R8.1, R9.1, R10.1; also elsewhere on the board
